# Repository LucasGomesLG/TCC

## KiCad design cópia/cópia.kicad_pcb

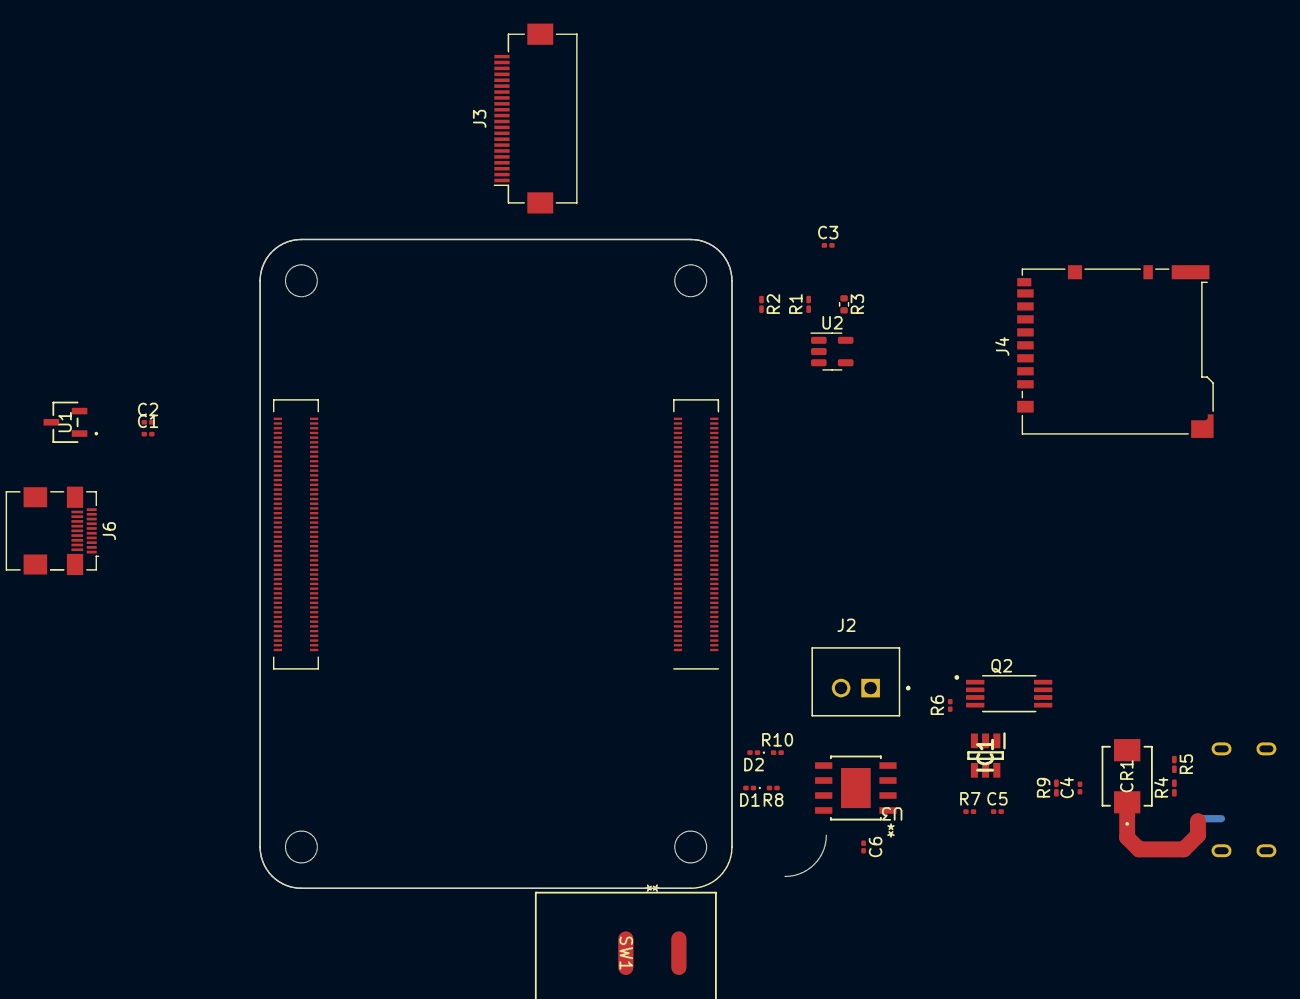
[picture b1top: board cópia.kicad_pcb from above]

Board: 2 copper layers, 48.0 x 55.0 mm, 31 parts (1 on the bottom side), 51 nets.

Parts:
C1, C2, C4, C5: 100nF; C_0201_0603Metric
C3, C6: 10uF; C_0201_0603Metric
CR1: SMBJ5.0A; DO-214AASMB_J-BEND_LTF
D1: LED_V; LED_0201_0603Metric
D2: LED_A; LED_0201_0603Metric
IC1: DW01; SOT95P280X135-6N
J1: USB_C_Receptacle_PowerOnly_6P; USB_C_Receptacle_GCT_USB4125-xx-x-0190_6P_TopMnt_Horizontal
J2: B2B-XH-A_LF__SN_
J3: Conn_01x22_Female; Hirose_FH12-22S-0.5SH_1x22-1MP_P0.50mm_Horizontal
J4: Micro_SD_Card_Det2; microSD_HC_Hirose_DM3BT-DSF-PEJS
J6: HDMI_D_1.4; HDMI_Micro-D_Molex_46765-0x01
Module1: ComputeModule4-CM4; Raspberry-Pi-4-Compute-Module
Q2: FS8205A; SOP65P640X120-8N
R1, R2: nf; R_0201_0603Metric_Pad0.64x0.40mm_HandSolder
R3: 12K 1%; R_0402_1005Metric
R4, R5: 5.1K; R_0201_0603Metric_Pad0.64x0.40mm_HandSolder
R6: 1.2k; R_0201_0603Metric
R7: 100ohm; R_0201_0603Metric
R8, R10: 1k; R_0201_0603Metric
R9: 1k; R_0201_0603Metric_Pad0.64x0.40mm_HandSolder
SW1: PRK22J5DBBNN; SW_PRK22J5DBBNN_ZFE
U1: RT9742SNGV; SOT_42SNGV_RIT
U2: RT9742GGJ5; SOT-23-5
U3: TP4056; SOP8-PP_TPW

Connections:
+1.8V: Module1.88 (+1.8v_(Output)), Module1.90 (+1.8v_(Output))
+5V: C1.1, C4.1, CR1.1, D1.2 (A), D2.2 (A), J1.A9 (VBUS), J1.B9 (VBUS), Module1.77 (+5v_(Input)), Module1.79 (+5v_(Input)), Module1.81 (+5v_(Input)), Module1.83 (+5v_(Input)), Module1.85 (+5v_(Input)), Module1.87 (+5v_(Input)), SW1.2, U1.1 (VIN), U3.4 (VCC), U3.8 (CE)
/+3.3v: J3.22, Module1.84 (+3.3v_(Output)), Module1.86 (+3.3v_(Output)), R1.2, R3.1, U2.5 (IN)
/CM4 GPIO/SD_CMD: J4.3 (CMD), Module1.62 (SD_CMD)
/CM4 GPIO/SD_DAT0: J4.7 (DAT0), Module1.63 (SD_DAT0)
/CM4 GPIO/SD_DAT1: J4.8 (DAT1), Module1.67 (SD_DAT1)
/CM4 GPIO/SD_DAT2: J4.1 (DAT2), Module1.69 (SD_DAT2)
/CM4 GPIO/SD_DAT3: J4.2 (DAT3/CD), Module1.61 (SD_DAT3)
/CM4 GPIO/SD_DET: Module1.76 (Reserved), R2.2
/CM4 GPIO/SD_PWR: C3.1, J4.4 (VDD), U2.1 (OUT)
/CM4 GPIO/SD_PWR_ON: Module1.75 (SD_PWR_ON), R3.2, U2.4 (EN)
/CM4 High Speed/DSI1_C_N: J3.8, Module1.187 (DSI1_C_N)
/CM4 High Speed/DSI1_C_P: J3.9, Module1.189 (DSI1_C_P)
/CM4 High Speed/DSI1_D0_N: J3.2, Module1.175 (DSI1_D0_N)
/CM4 High Speed/DSI1_D0_P: J3.3, Module1.177 (DSI1_D0_P)
/CM4 High Speed/DSI1_D1_N: J3.5, Module1.181 (DSI1_D1_N)
/CM4 High Speed/DSI1_D1_P: J3.6, Module1.183 (DSI1_D1_P)
/CM4 High Speed/DSI1_D2_N: J3.11, Module1.193 (DSI1_D2_N)
/CM4 High Speed/DSI1_D2_P: J3.12, Module1.195 (DSI1_D2_P)
/CM4 High Speed/DSI1_D3_N: J3.14, Module1.194 (DSI1_D3_N)
/CM4 High Speed/DSI1_D3_P: J3.15, Module1.196 (DSI1_D3_P)
/CM4 High Speed/HDMI0D2_P: J6.3 (D2+), Module1.170 (HDMI0_TX2_P)
/CM4 High Speed/HDMI0_CK_N: J6.14 (CK-), Module1.190 (HDMI0_CLK_N)
/CM4 High Speed/HDMI0_CK_P: J6.12 (CK+), Module1.188 (HDMI0_CLK_P)
/CM4 High Speed/HDMI0_D0_N: J6.11 (D0-), Module1.184 (HDMI0_TX0_N)
/CM4 High Speed/HDMI0_D0_P: J6.9 (D0+), Module1.182 (HDMI0_TX0_P)
/CM4 High Speed/HDMI0_D1_N: J6.8 (D1-), Module1.178 (HDMI0_TX1_N)
/CM4 High Speed/HDMI0_D1_P: J6.6 (D1+), Module1.176 (HDMI0_TX1_P)
/CM4 High Speed/HDMI0_D2_N: J6.5 (D2-), Module1.172 (HDMI0_TX2_N)
/CM4 High Speed/HDMI0_HOTPLUG: J6.1 (HPD/HEAC-), Module1.153 (HDMI0_HOTPLUG)
/CM4 High Speed/HDMI0_SCL: J6.17 (SCL), Module1.200 (HDMI0_SCL)
/CM4 High Speed/HDMI_5V: C2.1, J6.19 (+5V), U1.2 (VOUT)
/CM4 High Speed/SCL0: J3.20, Module1.80 (SCL0)
/CM4 High Speed/SDA0: J3.21, Module1.82 (SDA0)
/power /B+: C6.2, J2.2, R7.1, SW1.1, U3.5 (BAT)
/power /B-: J2.1, Q2.2, Q2.3
/power /CHRG_LED: R8.1, U3.7 (*CHRG)
/power /STDBY_LED: R10.2, U3.6 (*STDBY)
GND: C1.2, C2.2, C3.2, C4.2, C6.1, CR1.2, J1.A12 (GND), J1.B12 (GND), J1.S1 (SHIELD), J3.1, J3.4, J3.7, J3.10, J3.13, J3.16, J3.19, J4.6 (VSS), J4.11 (SHIELD), J6.4 (D2S), J6.7 (D1S), J6.10 (D0S), J6.13 (CKS), J6.16 (GND), J6.SH, Module1.1 (GND), Module1.2 (GND), Module1.7 (GND), Module1.8 (GND), Module1.13 (GND), Module1.14 (GND), Module1.22 (GND), Module1.23 (GND), Module1.32 (GND), Module1.33 (GND), Module1.42 (GND), Module1.43 (GND), Module1.52 (GND), Module1.53 (GND), Module1.59 (GND), Module1.60 (GND), Module1.65 (GND), Module1.66 (GND), Module1.71 (GND), Module1.74 (GND), Module1.98 (GND), Module1.107 (GND), Module1.108 (GND), Module1.113 (GND), Module1.114 (GND), Module1.119 (GND), Module1.120 (GND), Module1.125 (GND), Module1.126 (GND), Module1.131 (GND), Module1.132 (GND), Module1.137 (GND), Module1.138 (GND), Module1.144 (GND), Module1.150 (GND), Module1.155 (GND), Module1.156 (GND), Module1.161 (GND), Module1.162 (GND), Module1.167 (GND), Module1.168 (GND), Module1.173 (GND), Module1.174 (GND), Module1.179 (GND), Module1.180 (GND), Module1.185 (GND), Module1.186 (GND), Module1.191 (GND), Module1.192 (GND), Module1.197 (GND), Module1.198 (GND), Q2.6, Q2.7, R4.2, R5.2, R6.2, R9.2, U1.3 (GND), U2.2 (GND), U3.1 (TEMP), U3.3 (GND), U3.EPAD
unnamed: D1.1 (K), R8.2
unnamed: D2.1 (K), R10.1
unnamed: IC1.2 (CSI), R9.1
unnamed: IC1.3 (OC), Q2.5
unnamed: IC1.1 (OD), Q2.4
unnamed: C5.1, IC1.5 (VDD), R7.2
unnamed: C5.2, IC1.6 (VSS)
unnamed: J1.A5 (CC1), R5.1
unnamed: J1.B5 (CC2), R4.1
unnamed: J4.10 (DET_A), R1.1
unnamed: J4.9 (DET_B), R2.1
unnamed: R6.1, U3.2 (PROG)

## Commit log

2025-06-14 primeiro commit

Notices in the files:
cópia/cópia.kicad_pcb:
creativecommons.org/licenses/by/4.0
License: CC BY 4.0
